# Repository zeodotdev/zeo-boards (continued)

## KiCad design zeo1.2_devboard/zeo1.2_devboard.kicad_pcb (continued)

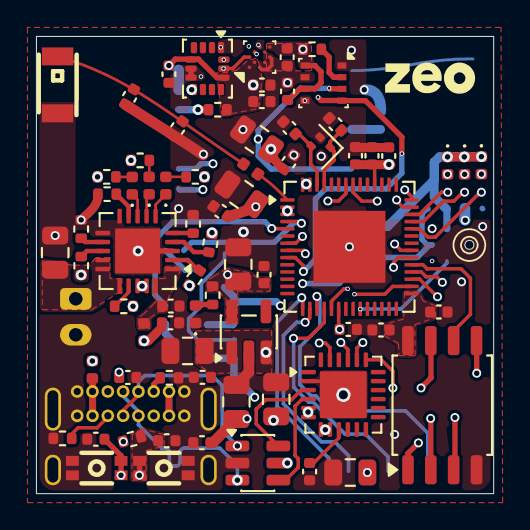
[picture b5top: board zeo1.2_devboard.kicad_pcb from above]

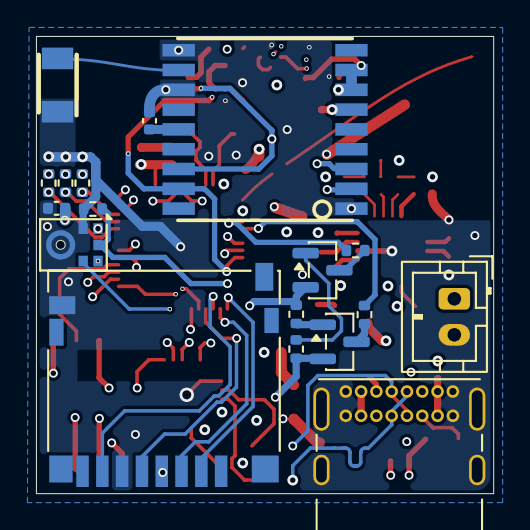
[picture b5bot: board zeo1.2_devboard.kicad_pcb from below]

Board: 4 copper layers, 25.4 x 25.4 mm, 91 parts (18 on the bottom side), 70 nets.

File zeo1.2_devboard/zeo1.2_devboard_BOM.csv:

"Id";"Designator";"Footprint";"Quantity";"Designation";"Supplier and ref";
1;"B";"KEY-SMD_4P-L2.6-W1.6-P0.80-LS3.0";1;"Boot";;;
2;"C1, C4, C16, C21, C37";"C_0805_2012Metric";5;"10uF";;;
3;"C2, C3, C5, C7, C8, C9, C10, C13, C17, C18, C20, C22, C23, C24, C26, C31, C32, C33, C34, C36";"C_0402_1005Metric";20;"0.1uF";;;
4;"C6, C14, C25";"C_0402_1005Metric";3;"1uF";;;
5;"C19";"C_0805_2012Metric";1;"4.7uF";;;
6;"C27, C28, C38";"C_0402_1005Metric";3;"10pF";;;
7;"C29";"C_0402_1005Metric";1;"0.5pF";;;
8;"C30";"C_0402_1005Metric";1;"1.2pF";;;
9;"D1, D2, D5";"LED_0402_1005Metric";3;"Red";;;
10;"D3, D6";"LED_0402_1005Metric";2;"Green";;;
11;"D4, D7";"LED_0402_1005Metric";2;"Blue";;;
12;"F1";"Fuse_0402_1005Metric";1;"1.1A PTC";;;
13;"FB1";"L_0402_1005Metric";1;"33R@100MHz";;;
14;"J1";"USB_C_Receptacle_Amphenol_12401610E4-2A_CircularHoles";1;"USB_C_Receptacle_USB2.0_14P";;;
15;"J2";"JST_ZH_B2B-ZR_1x02_P1.50mm_Vertical";1;"JST-PH Battery";;;
16;"J4";"microSD_HC_Hirose_DM3D-SF";1;"Micro_SD";;;
17;"L1";"L_0402_1005Metric";1;"2.7nH";;;
18;"MK2";"InvenSense_ICS-43434-6_3.5x2.65mm";1;"ICS-43434";;;
19;"Q2, Q3";"SOT-23";2;"BC817";;;
20;"R";"KEY-SMD_4P-L2.6-W1.6-P0.80-LS3.0";1;"RESET";;;
21;"R1, R2";"R_0402_1005Metric";2;"5.1k";;;
22;"R3";"R_0402_1005Metric";1;"2k";;;
23;"R4, R9, R16";"R_0402_1005Metric";3;"100k";;;
24;"R5";"R_0402_1005Metric";1;"20k";;;
25;"R6, R7, R8, R14, R19, R22, R23, R24, R25";"R_0402_1005Metric";9;"10k";;;
26;"R10, R20, R21, R26";"R_0402_1005Metric";4;"330R";;;
27;"R11, R12, R13";"R_0402_1005Metric";3;"470R";;;
28;"R15";"R_0402_1005Metric";1;"0R";;;
29;"TP2, TP3, TP4, TP6, TP7, TP8, TP9";"TestPoint_Pad_1.0x1.0mm";7;"TestPoint";;;
30;"U1";"SOT-23-5";1;"AP2112K-3.3";;;
31;"U2";"QFN-20-1EP_4x4mm_P0.5mm_EP2.5x2.5mm";1;"MCP73871";;;
32;"U3";"Bosch_LGA-8_2.5x2.5mm_P0.65mm_ClockwisePinNumbering";1;"BME280";;;
33;"U5";"SOT-23-6";1;"USBLC6-2SC6";;;
34;"U6";"QFN-24-1EP_4x4mm_P0.5mm_EP2.6x2.6mm";1;"CP2102N-QFN24";;;
35;"U7";"SOIC-8_5.3x5.3mm_P1.27mm";1;"W25Q128JVSIQ";;;
36;"U8";"ANT-SMD_L3.2-W1.6";1;"ANT3216LL00R2400A";;;
37;"U9";"SMD-18_L10.1-W9.7-P1.10-TL_SKG09F";1;"MAX-M10S-00B";;;
38;"U10";"QFN-56-1EP_7x7mm_P0.4mm_EP4x4mm";1;"ESP32-S3";;;
39;"U11";"LGA-14_3x2.5mm_P0.5mm_LayoutBorder3x4y";1;"LSM6DS3";;;
40;"U12";"WLCSP-12_1.56x1.56mm_P0.4mm";1;"BMM150";;;
41;"U13";"ANT-SMD_L3.2-W1.6-2";1;"W3011";;;
42;"Y1";"Crystal_SMD_WE_IQXC-240-4Pin_1.2x1.0mm";1;"40MHz";;;

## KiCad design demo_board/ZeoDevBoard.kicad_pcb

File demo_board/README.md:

# ZeoDevBoard

ESP32-S3 development board with onboard BME280 (temperature, humidity, pressure) and LSM6DS3 (6-axis IMU) sensors. This repo contains the designs, ESP-IDF firmware, and a Python plotter for visualization.

## Hardware

- **MCU:** ESP32-S3-WROOM-1 (Wi-Fi + BLE)
- **Sensors:** BME280 (I2C 0x76), LSM6DS3 (I2C 0x6A) on shared bus (GPIO8 SDA, GPIO9 SCL)
- **Power:** USB-C with MCP73871 LiPo charger + AP2112K 3.3V LDO — runs from USB or battery
- **Interface:** USB-C for flashing/debug, BOOT + RESET buttons

## Firmware

Streams sensor data over Wi-Fi as UDP broadcast JSON packets on port 12345.

- **IMU:** 100 Hz — accelerometer (m/s²) + gyroscope (deg/s)
- **BME280:** 1 Hz — temperature (°C), humidity (%RH), pressure (hPa)

### Prerequisites

- [ESP-IDF v5.4](https://docs.espressif.com/projects/esp-idf/en/v5.4/esp32s3/get-started/)

### Build and Flash

```bash
# Source ESP-IDF environment
source ~/esp/esp-idf/export.sh

# Enter firmware directory
cd firmware

# Set target and configure Wi-Fi credentials
idf.py set-target esp32s3
idf.py menuconfig  # Navigate to "ZeoDevBoard Configuration" → set SSID and password

# Build
idf.py build

# Flash (use esptool.py directly if idf.py has port permission issues)
esptool.py --chip esp32s3 -p /dev/ttyACM0 -b 460800 \
  --before default_reset --after hard_reset write_flash \
  --flash_mode dio --flash_size 2MB --flash_freq 80m \
  0x0 build/bootloader/bootloader.bin \
  0x8000 build/partition_table/partition-table.bin \
  0x10000 build/zeodevboard.bin

# Monitor serial output (optional)
idf.py -p /dev/ttyACM0 monitor
```

### Wireless Operation

Once flahsed, the board can run on battery power.

## Plotter

Displays 6 live panels: Accelerometer XYZ, Gyroscope XYZ, Temperature, Humidity, Pressure, and a status panel with packet counts.

### Run

```bash
cd plotter
python3 -m venv venv
./venv/bin/pip install -r requirements.txt
./venv/bin/python plotter.py
```

The plotter listens on UDP port 12345. Make sure your machine is on the same network as the board.

### UDP Packet Format

IMU (100 Hz):
```json
{"type":"imu","ts":1234,"ax":0.12,"ay":-0.05,"az":-9.81,"gx":1.2,"gy":-0.3,"gz":0.1}
```

Environment (1 Hz):
```json
{"type":"env","ts":1234,"temp":25.3,"hum":45.2,"press":1013.4}
```

`ts` is milliseconds since boot.

## Project Structure

```
demo_board/
├── firmware/
│   ├── CMakeLists.txt
│   ├── sdkconfig.defaults
│   └── main/
│       ├── CMakeLists.txt
│       ├── Kconfig.projbuild      # Wi-Fi SSID/password config
│       ├── main.c                 # App entry, FreeRTOS tasks
│       ├── wifi.c / wifi.h        # Wi-Fi STA connection
│       ├── sensors.c / sensors.h  # BME280 + LSM6DS3 I2C drivers
│       └── udp_sender.c / udp_sender.h  # UDP broadcast
├── plotter/
│   ├── plotter.py
│   └── requirements.txt
├── ZeoDevBoard.kicad_sch          # Root schematic
├── mcu.kicad_sch                  # MCU sheet
├── power_supply.kicad_sch         # Power supply sheet
├── sensors.kicad_sch              # Sensors sheet
├── ZeoDevBoard.kicad_pcb          # PCB layout
└── README.md
```

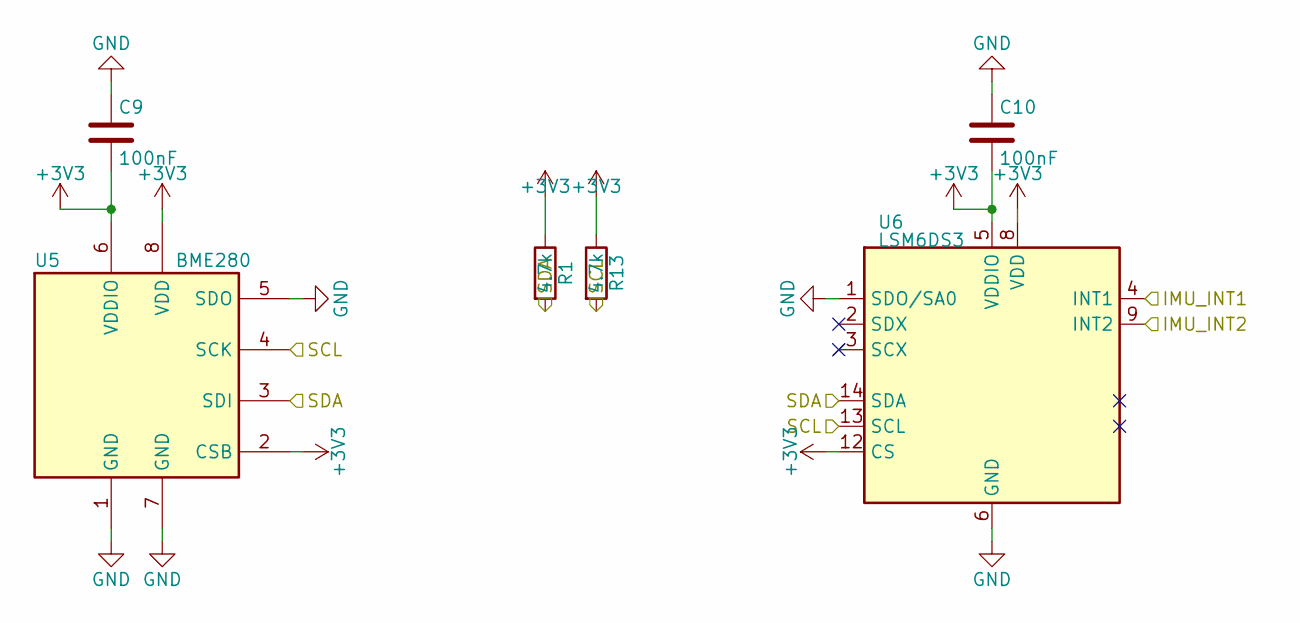
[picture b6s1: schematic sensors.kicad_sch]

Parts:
C9, C10: 100nF; C_0402_1005Metric
R1, R13: 4.7k; R_0603_1608Metric
U5: BME280; Bosch_LGA-8_2.5x2.5mm_P0.65mm_ClockwisePinNumbering
U6: LSM6DS3; LGA-14_3x2.5mm_P0.5mm_LayoutBorder3x4y

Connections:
+3V3: C9.2, C10.2, R1.1, R13.1, U5.2 (CSB), U5.6 (VDDIO), U5.8 (VDD), U6.5 (VDDIO), U6.8 (VDD), U6.12 (CS); also elsewhere on the board
/IMU_INT1: U6.4 (INT1); also elsewhere on the board
/IMU_INT2: U6.9 (INT2); also elsewhere on the board
/SCL: R13.2, U5.4 (SCK), U6.13 (SCL); also elsewhere on the board
/SDA: R1.2, U5.3 (SDI), U6.14 (SDA); also elsewhere on the board

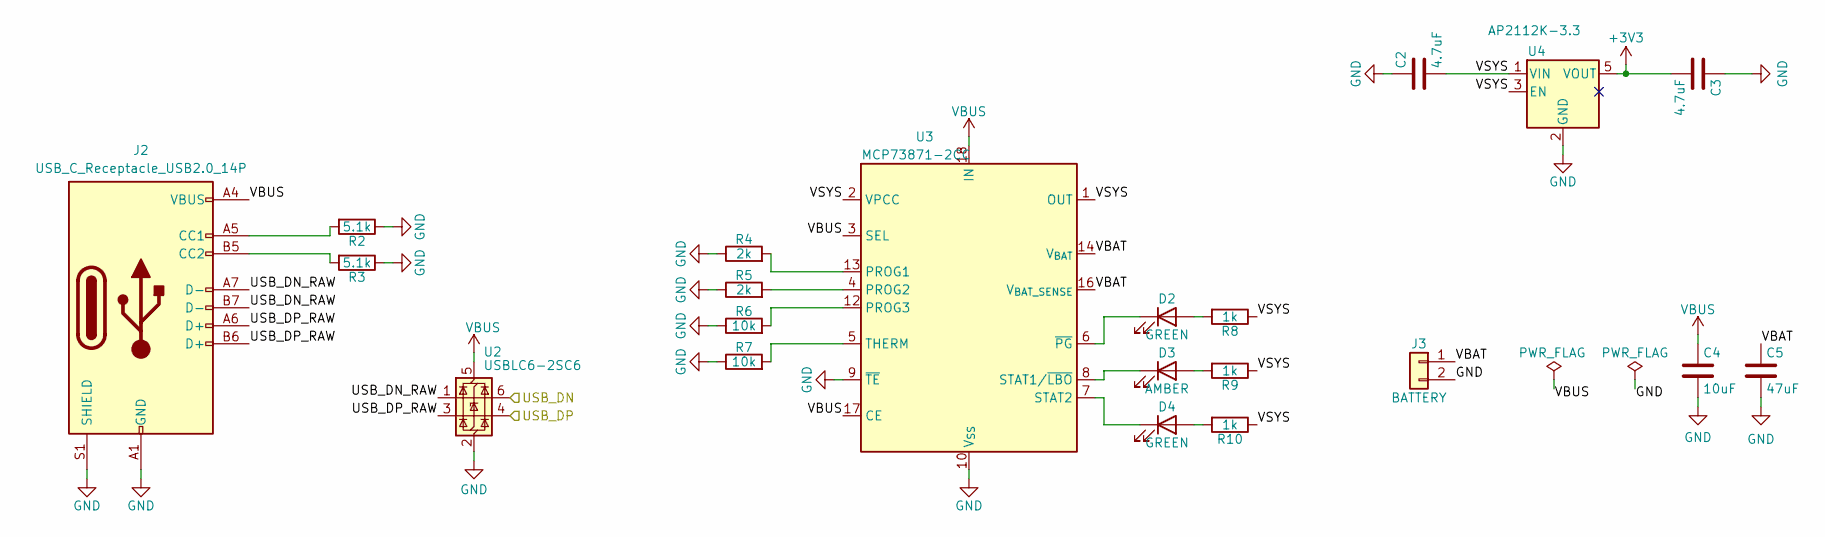
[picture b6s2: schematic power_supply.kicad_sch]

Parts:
C2, C3: 4.7uF; C_0805_2012Metric
C4: 10uF; C_0805_2012Metric
C5: 47uF; C_1206_3216Metric
D2, D4: GREEN; LED_0603_1608Metric
D3: AMBER; LED_0603_1608Metric
J2: USB_C_Receptacle_USB2.0_14P; USB_C_Receptacle_Amphenol_12401610E4-2A
J3: BATTERY; JST_PH_B2B-PH-K_1x02_P2.00mm_Vertical
R2, R3: 5.1k; R_0603_1608Metric
R4, R5: 2k; R_0603_1608Metric
R6, R7: 10k; R_0603_1608Metric
R8, R9, R10: 1k; R_0603_1608Metric
U2: USBLC6-2SC6; SOT-23-6
U3: MCP73871-2CC; QFN-20-1EP_4x4mm_P0.5mm_EP2.5x2.5mm
U4: AP2112K-3.3; SOT-23-5

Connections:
+3V3: C3.2, U4.5 (VOUT); also elsewhere on the board
/Power Supply/USB_DN_RAW: J2.A7 (D-), J2.B7 (D-), U2.1 (I/O1)
/Power Supply/USB_DP_RAW: J2.A6 (D+), J2.B6 (D+), U2.3 (I/O2)
/Power Supply/VBAT: C5.1, J3.1, U3.14 (V_{BAT}), U3.15 (V_{BAT}), U3.16 (V_{BAT_SENSE})
/Power Supply/VSYS: C2.2, R8.1, R9.1, R10.1, U3.1 (OUT), U3.2 (VPCC), U3.20 (OUT), U4.1 (VIN), U4.3 (EN)
/USB_DN: U2.6 (I/O1); also elsewhere on the board
/USB_DP: U2.4 (I/O2); also elsewhere on the board
unnamed: D2.2 (A), R8.2
unnamed: D2.1 (K), U3.6 (~PG)
unnamed: D3.2 (A), R9.2
unnamed: D3.1 (K), U3.8 (STAT1/~LBO)
unnamed: D4.2 (A), R10.2
unnamed: D4.1 (K), U3.7 (STAT2)
unnamed: J2.A5 (CC1), R2.2
unnamed: J2.B5 (CC2), R3.2
unnamed: R4.2, U3.13 (PROG1)
unnamed: R5.2, U3.4 (PROG2)
unnamed: R6.2, U3.12 (PROG3)
unnamed: R7.2, U3.5 (THERM)

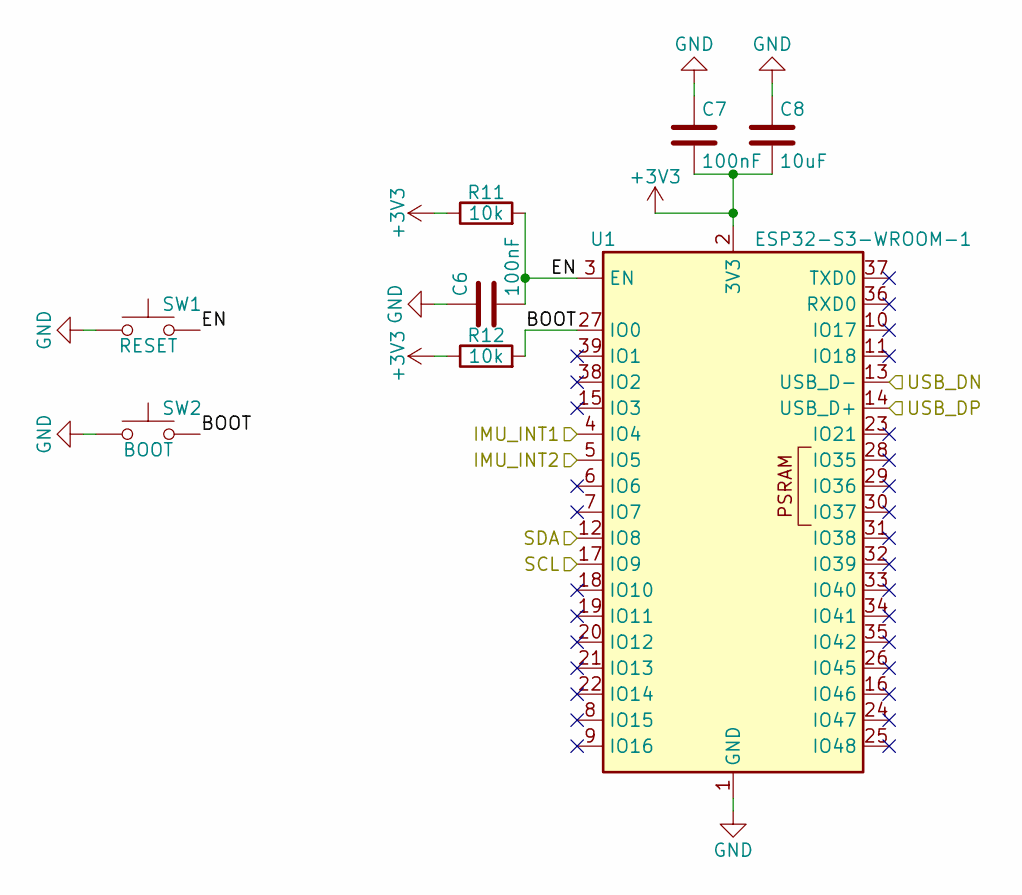
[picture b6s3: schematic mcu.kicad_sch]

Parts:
C6, C7: 100nF; C_0402_1005Metric
C8: 10uF; C_0805_2012Metric
R11, R12: 10k; R_0603_1608Metric
SW1: RESET; SW_SPST_B3U-1000P-B
SW2: BOOT; SW_SPST_B3U-1000P-B
U1: ESP32-S3-WROOM-1

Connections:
+3V3: C7.2, C8.2, R11.1, R12.1, U1.2 (3V3); also elsewhere on the board
/IMU_INT1: U1.4 (IO4); also elsewhere on the board
/IMU_INT2: U1.5 (IO5); also elsewhere on the board
/MCU/BOOT: R12.2, SW2.2, U1.27 (IO0)
/MCU/EN: C6.2, R11.2, SW1.2, U1.3 (EN)
/SCL: U1.17 (IO9); also elsewhere on the board
/SDA: U1.12 (IO8); also elsewhere on the board
/USB_DN: U1.13 (USB_D-); also elsewhere on the board
/USB_DP: U1.14 (USB_D+); also elsewhere on the board

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
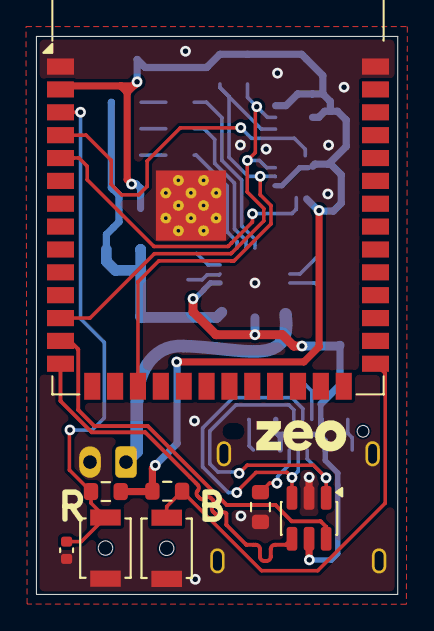
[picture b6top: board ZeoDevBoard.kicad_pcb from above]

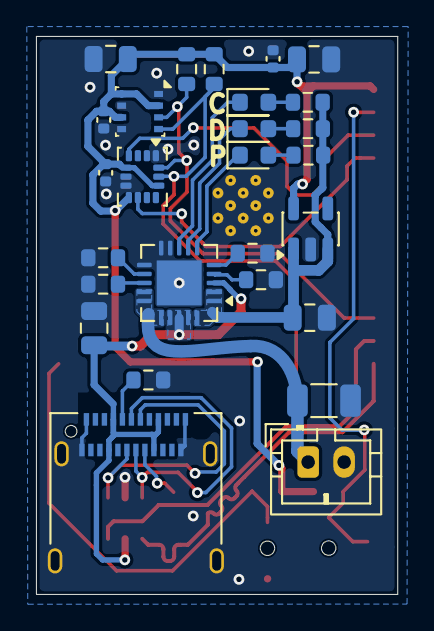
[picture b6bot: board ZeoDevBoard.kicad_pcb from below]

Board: 2 copper layers, 20.1 x 31.0 mm, 35 parts (27 on the bottom side), 27 nets.

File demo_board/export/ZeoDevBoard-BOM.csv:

Id,Designator,Footprint,Quantity,Comment,Supplier and ref
1,"C2, C3",C_0805_2012Metric,2,4.7uF,
2,"C4, C8",C_0805_2012Metric,2,10uF,
3,C5,C_1206_3216Metric,1,47uF,
4,"C6, C7, C9, C10",C_0402_1005Metric,4,100nF,
5,"D2, D4",LED_0603_1608Metric,2,GREEN,
6,D3,LED_0603_1608Metric,1,AMBER,
7,J2,USB_C_Receptacle_Amphenol_12401610E4-2A,1,USB_C_Receptacle_USB2.0_14P,
8,J3,JST_PH_B2B-PH-K_1x02_P2.00mm_Vertical,1,BATTERY,
9,"R1, R13",R_0603_1608Metric,2,4.7k,
10,"R2, R3",R_0603_1608Metric,2,5.1k,
11,"R4, R5",R_0603_1608Metric,2,2k,
12,"R6, R7, R11, R12",R_0603_1608Metric,4,10k,
13,"R8, R9, R10",R_0603_1608Metric,3,1k,
14,SW1,SW_SPST_B3U-1000P-B,1,RESET,
15,SW2,SW_SPST_B3U-1000P-B,1,BOOT,
16,U1,ESP32-S3-WROOM-1,1,ESP32-S3-WROOM-1,
17,U2,SOT-23-6,1,USBLC6-2SC6,
18,U3,QFN-20-1EP_4x4mm_P0.5mm_EP2.5x2.5mm,1,MCP73871-2CC,
19,U4,SOT-23-5,1,AP2112K-3.3,
20,U5,Bosch_LGA-8_2.5x2.5mm_P0.65mm_ClockwisePinNumbering,1,BME280,
21,U6,LGA-14_3x2.5mm_P0.5mm_LayoutBorder3x4y,1,LSM6DS3,

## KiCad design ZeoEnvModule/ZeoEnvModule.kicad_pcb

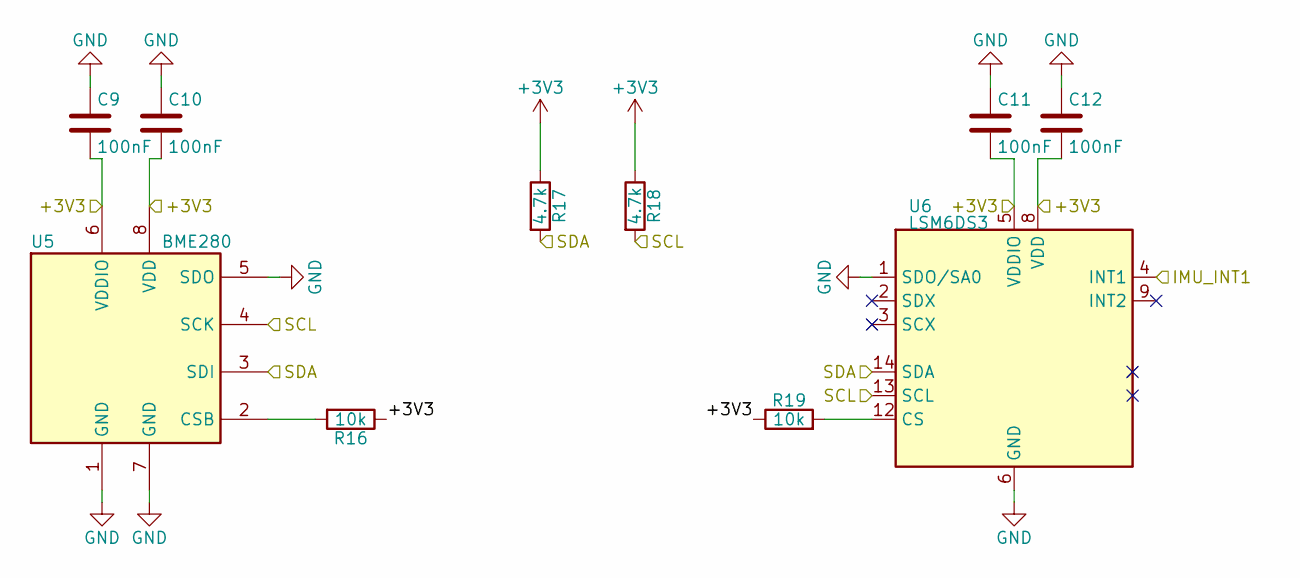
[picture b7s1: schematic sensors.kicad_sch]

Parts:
C9, C10, C11, C12: 100nF; C_0402_1005Metric
R16, R19: 10k; R_0402_1005Metric
R17, R18: 4.7k; R_0402_1005Metric
U5: BME280; Bosch_LGA-8_2.5x2.5mm_P0.65mm_ClockwisePinNumbering
U6: LSM6DS3; LGA-14_3x2.5mm_P0.5mm_LayoutBorder3x4y

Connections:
+3V3: C9.2, C10.2, C11.2, C12.2, R16.1, R17.1, R18.1, R19.1, U5.6 (VDDIO), U5.8 (VDD), U6.5 (VDDIO), U6.8 (VDD); also elsewhere on the board
/IMU_INT1: U6.4 (INT1); also elsewhere on the board
/SCL: R18.2, U5.4 (SCK), U6.13 (SCL); also elsewhere on the board
/SDA: R17.2, U5.3 (SDI), U6.14 (SDA); also elsewhere on the board
unnamed: R16.2, U5.2 (CSB)
unnamed: R19.2, U6.12 (CS)

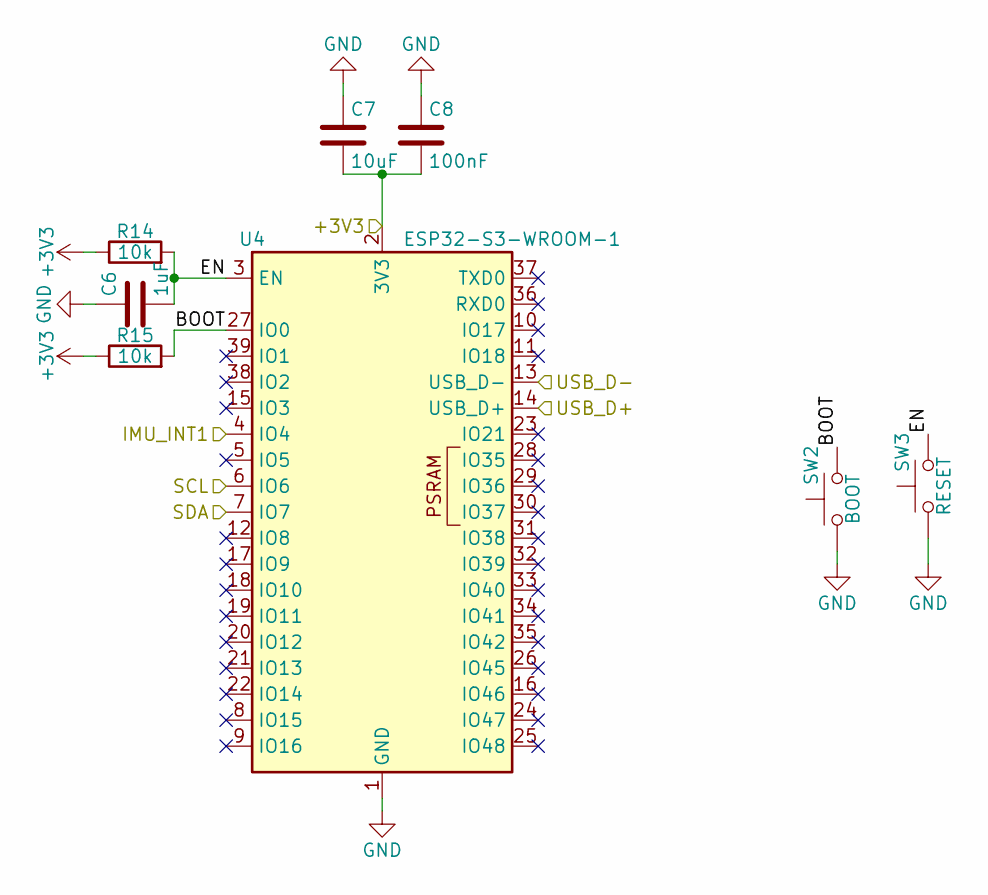
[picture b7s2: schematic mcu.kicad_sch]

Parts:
C6: 1uF; C_0402_1005Metric
C7: 10uF; C_0805_2012Metric
C8: 100nF; C_0402_1005Metric
R14, R15: 10k; R_0402_1005Metric
SW2: BOOT; SW_SPST_B3U-1000P-B
SW3: RESET; SW_SPST_B3U-1000P-B
U4: ESP32-S3-WROOM-1

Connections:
+3V3: C7.2, C8.2, R14.1, R15.1, U4.2 (3V3); also elsewhere on the board
/IMU_INT1: U4.4 (IO4); also elsewhere on the board
/MCU/BOOT: R15.2, SW2.2, U4.27 (IO0)
/MCU/EN: C6.2, R14.2, SW3.2, U4.3 (EN)
/SCL: U4.6 (IO6); also elsewhere on the board
/SDA: U4.7 (IO7); also elsewhere on the board
/USB_D+: U4.14 (USB_D+); also elsewhere on the board
/USB_D-: U4.13 (USB_D-); also elsewhere on the board

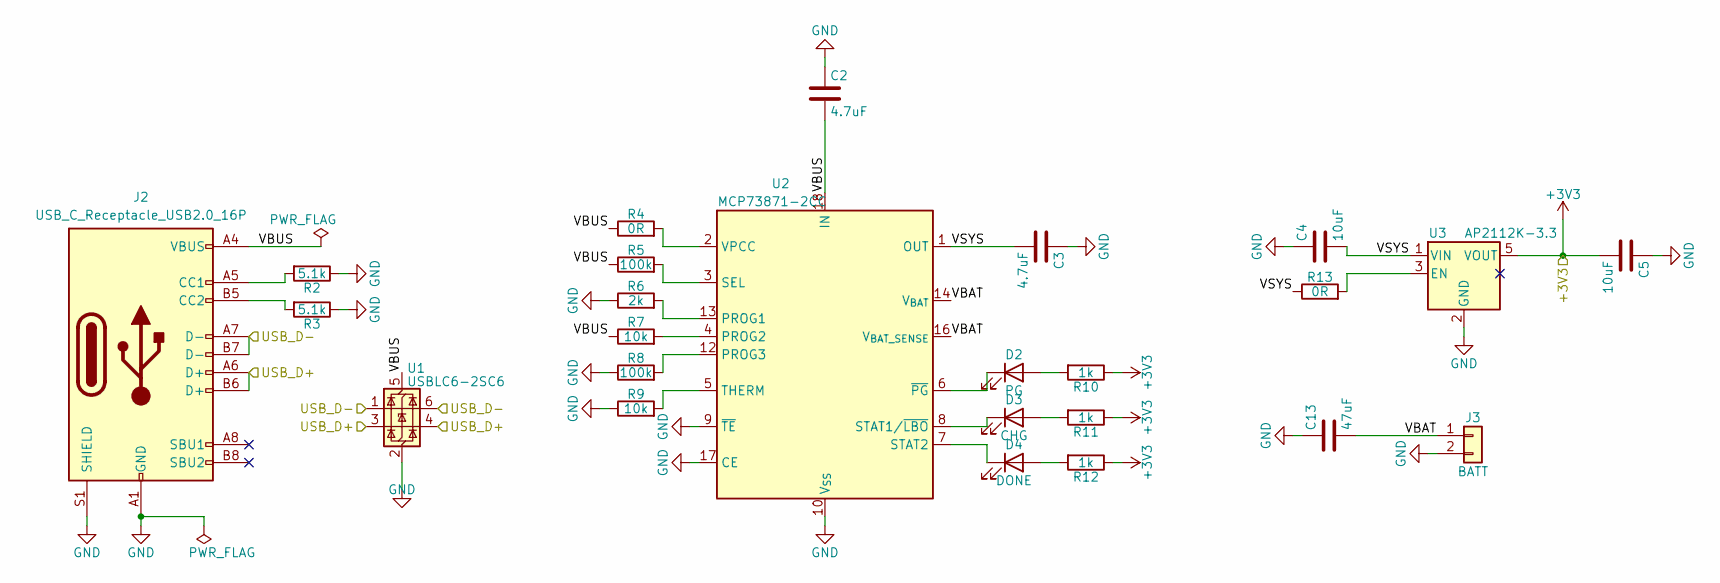
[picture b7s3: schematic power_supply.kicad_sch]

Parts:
C2, C3: 4.7uF; C_0603_1608Metric
C4, C5: 10uF; C_0805_2012Metric
C13: 47uF; C_1210_3225Metric
D2: PG; LED_0603_1608Metric
D3: CHG; LED_0603_1608Metric
D4: DONE; LED_0603_1608Metric
J2: USB_C_Receptacle_USB2.0_16P; USB_C_Receptacle_HRO_TYPE-C-31-M-12
J3: BATT; JST_PH_B2B-PH-K_1x02_P2.00mm_Vertical
R2, R3: 5.1k; R_0402_1005Metric
R4, R13: 0R; R_0402_1005Metric
R5, R8: 100k; R_0402_1005Metric
R6: 2k; R_0402_1005Metric
R7, R9: 10k; R_0402_1005Metric
R10, R11, R12: 1k; R_0402_1005Metric
U1: USBLC6-2SC6; SOT-23-6
U2: MCP73871-2CC; QFN-20-1EP_4x4mm_P0.5mm_EP2.5x2.5mm
U3: AP2112K-3.3; SOT-23-5

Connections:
+3V3: C5.2, R10.1, R11.1, R12.1, U3.5 (VOUT); also elsewhere on the board
/Power Supply/VBAT: C13.2, J3.1, U2.14 (V_{BAT}), U2.15 (V_{BAT}), U2.16 (V_{BAT_SENSE})
/Power Supply/VSYS: C3.2, C4.2, R13.1, U2.1 (OUT), U2.20 (OUT), U3.1 (VIN)
/USB_D+: J2.A6 (D+), J2.B6 (D+), U1.3 (I/O2), U1.4 (I/O2); also elsewhere on the board
/USB_D-: J2.A7 (D-), J2.B7 (D-), U1.1 (I/O1), U1.6 (I/O1); also elsewhere on the board
unnamed: D2.2 (A), R10.2
unnamed: D2.1 (K), U2.6 (~PG)
unnamed: D3.2 (A), R11.2
unnamed: D3.1 (K), U2.8 (STAT1/~LBO)
unnamed: D4.2 (A), R12.2
unnamed: D4.1 (K), U2.7 (STAT2)
unnamed: J2.A5 (CC1), R2.2
unnamed: J2.B5 (CC2), R3.2
unnamed: R6.2, U2.13 (PROG1)
unnamed: R7.2, U2.4 (PROG2)
unnamed: R8.2, U2.12 (PROG3)
unnamed: R5.2, U2.3 (SEL)
unnamed: R9.2, U2.5 (THERM)
unnamed: R4.2, U2.2 (VPCC)
unnamed: R13.2, U3.3 (EN)

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
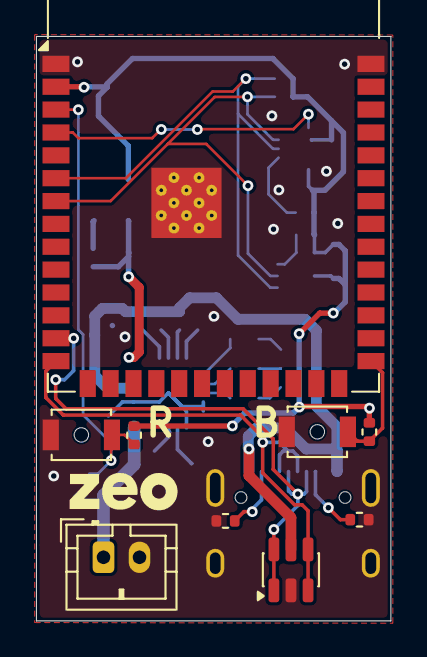
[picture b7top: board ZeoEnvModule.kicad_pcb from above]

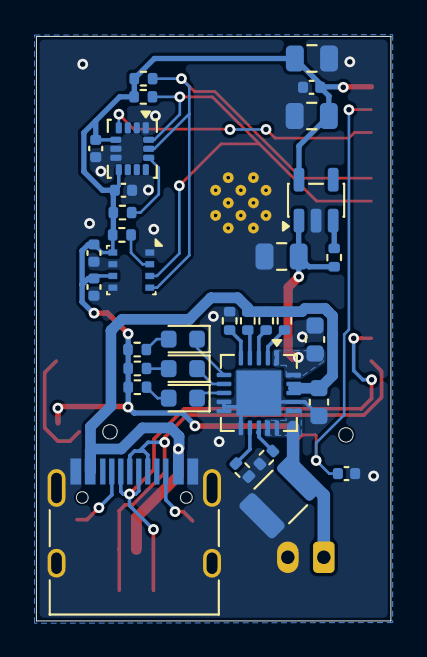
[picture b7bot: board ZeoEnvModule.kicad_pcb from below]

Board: 2 copper layers, 19.7 x 32.5 mm, 43 parts (34 on the bottom side), 29 nets.

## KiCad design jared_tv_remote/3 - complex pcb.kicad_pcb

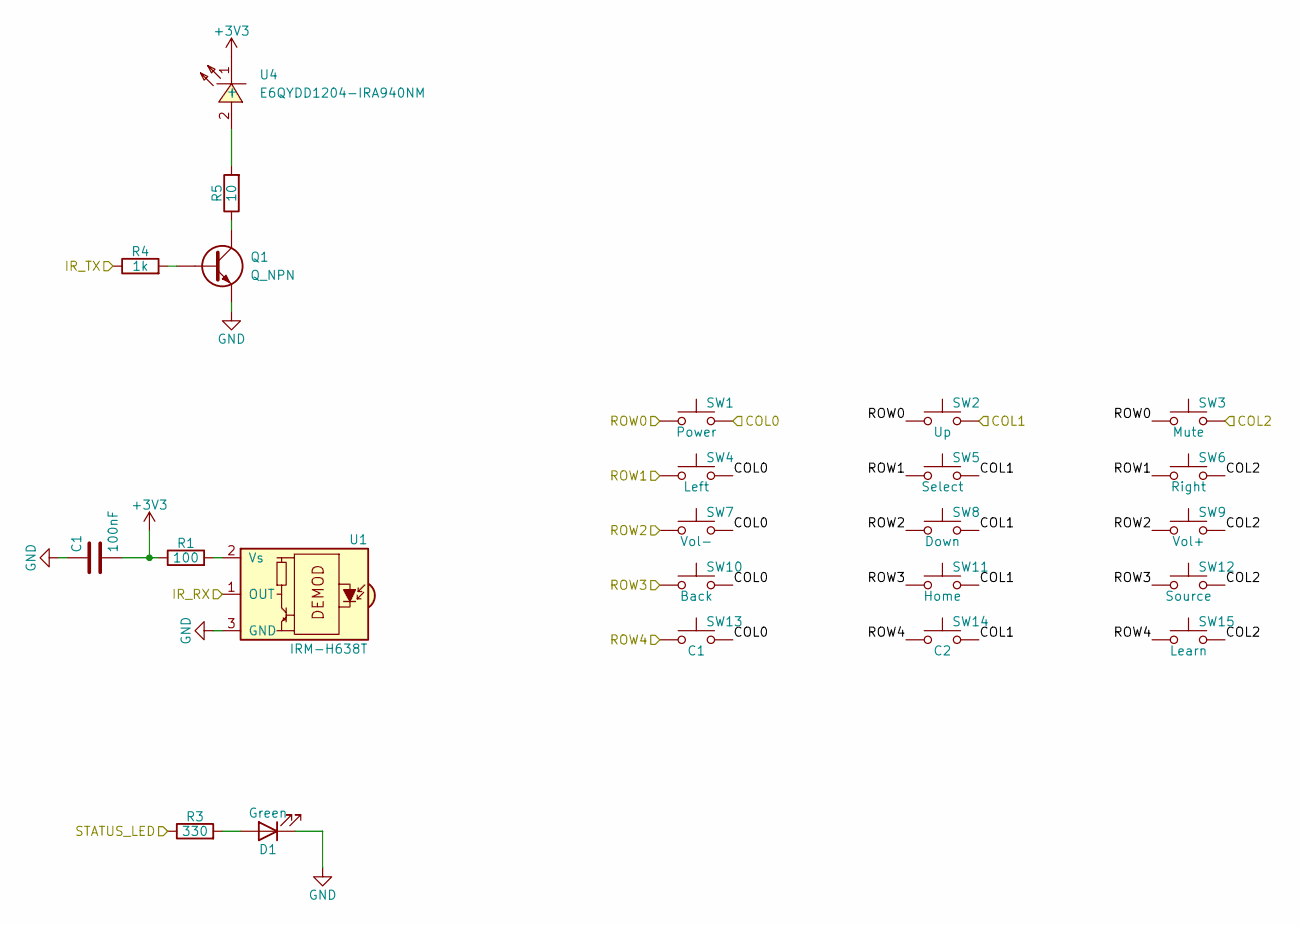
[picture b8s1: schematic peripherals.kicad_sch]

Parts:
C1: 100nF; C_0402_1005Metric
D1: Green; LED_0603_1608Metric
Q1: Q_NPN; SOT-23
R1: 100; R_0402_1005Metric
R3: 330; R_0402_1005Metric
R4: 1k; R_0402_1005Metric
R5: 10; R_0805_2012Metric
SW1: Power; SW_SPST_B3U-1000P
SW2: Up; SW_SPST_B3U-1000P
SW3: Mute; SW_SPST_B3U-1000P
SW4: Left; SW_SPST_B3U-1000P
SW5: Select; SW_SPST_B3U-1000P
SW6: Right; SW_SPST_B3U-1000P
SW7: Vol-; SW_SPST_B3U-1000P
SW8: Down; SW_SPST_B3U-1000P
SW9: Vol+; SW_SPST_B3U-1000P
SW10: Back; SW_SPST_B3U-1000P
SW11: Home; SW_SPST_B3U-1000P
SW12: Source; SW_SPST_B3U-1000P
SW13: C1; SW_SPST_B3U-1000P
SW14: C2; SW_SPST_B3U-1000P
SW15: Learn; SW_SPST_B3U-1000P
U1: IRM-H638T; Everlight_IRM-H6xxT
U4: E6QYDD1204-IRA940NM; LED-SMD_L3.2-W2.1-R-FD; LCSC Part C396649

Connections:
+3V3: C1.2, R1.1, U4.1 (-); also elsewhere on the board
/COL0: SW1.2, SW4.2, SW7.2, SW10.2, SW13.2; also elsewhere on the board
/COL1: SW2.2, SW5.2, SW8.2, SW11.2, SW14.2; also elsewhere on the board
/COL2: SW3.2, SW6.2, SW9.2, SW12.2, SW15.2; also elsewhere on the board
/IR_RX: U1.1 (OUT); also elsewhere on the board
/IR_TX: R4.1; also elsewhere on the board
/ROW0: SW1.1, SW2.1, SW3.1; also elsewhere on the board
/ROW1: SW4.1, SW5.1, SW6.1; also elsewhere on the board
/ROW2: SW7.1, SW8.1, SW9.1; also elsewhere on the board
/ROW3: SW10.1, SW11.1, SW12.1; also elsewhere on the board
/ROW4: SW13.1, SW14.1, SW15.1; also elsewhere on the board
/STATUS_LED: R3.1; also elsewhere on the board
unnamed: D1.2 (A), R3.2
unnamed 16: R5.2, U4.2 (+); also elsewhere on the board
unnamed: Q1.1 (B), R4.2
unnamed: Q1.2 (C), R5.1
unnamed: R1.2, U1.2 (Vs)

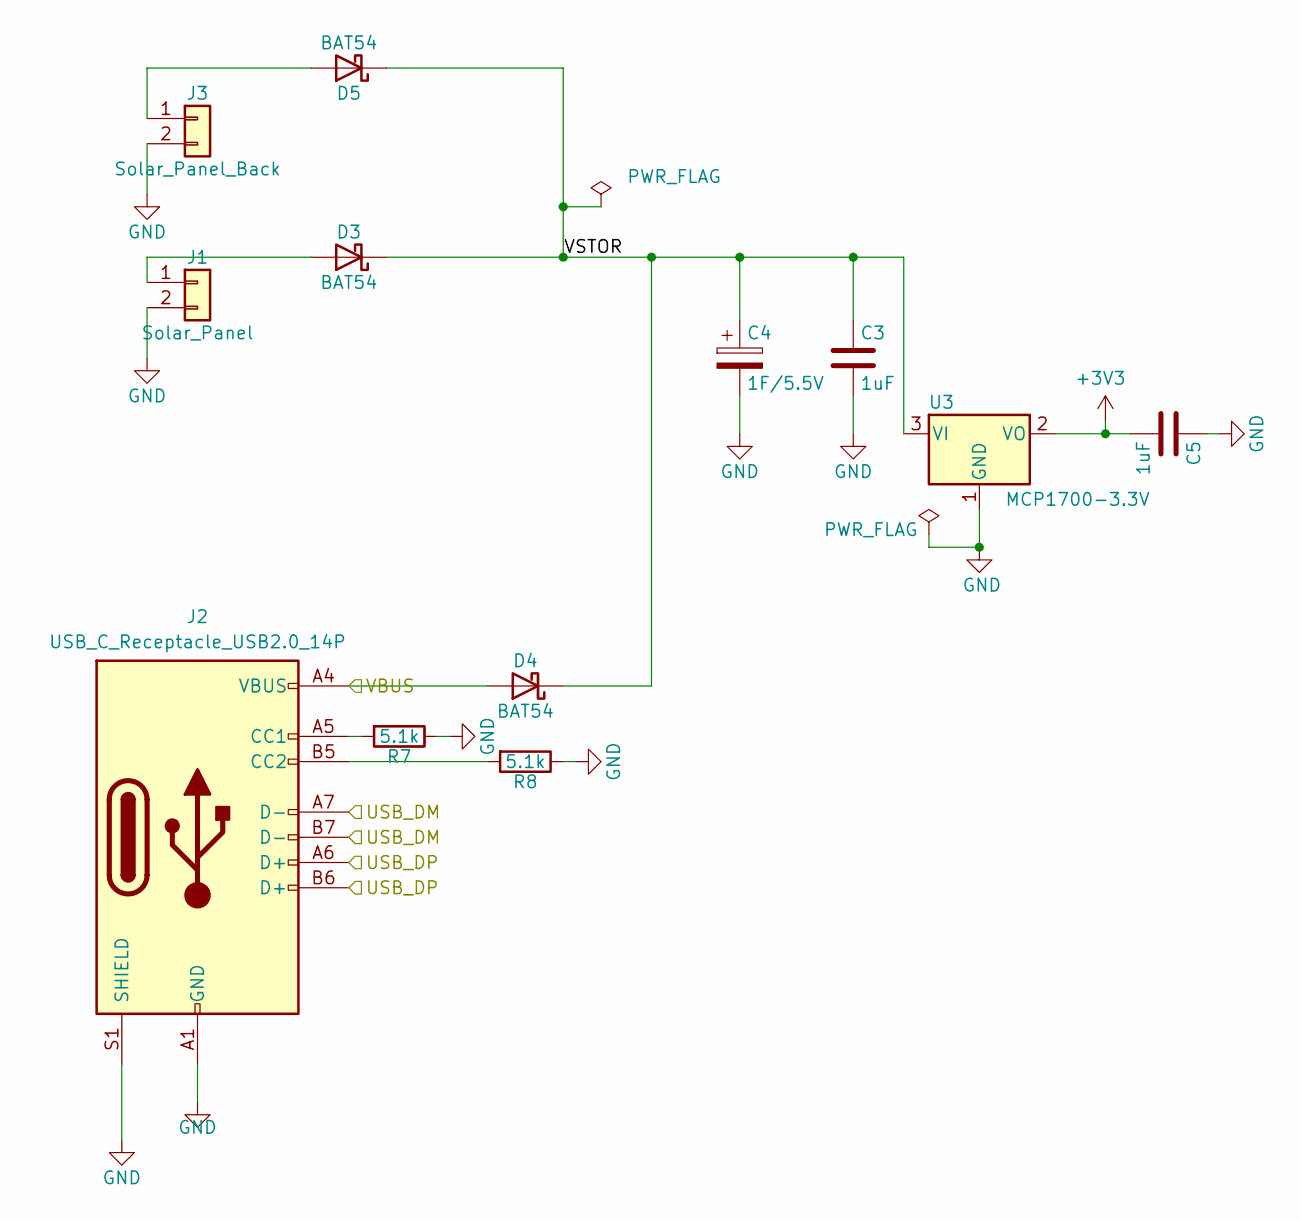
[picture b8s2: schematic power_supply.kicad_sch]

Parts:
C3, C5: 1uF; C_0402_1005Metric
C4: 1F/5.5V; C_1210_3225Metric
D3, D4, D5: BAT54; D_SOD-323
J1: Solar_Panel; SolderWire-0.5sqmm_1x02_P4.6mm_D0.9mm_OD2.1mm
J2: USB_C_Receptacle_USB2.0_14P; USB_C_Receptacle_HRO_TYPE-C-31-M-12
J3: Solar_Panel_Back; SolderWire-0.5sqmm_1x02_P4.6mm_D0.9mm_OD2.1mm
R7, R8: 5.1k; R_0402_1005Metric
U3: MCP1700-3.3V; SOT-23

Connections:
+3V3: C5.2, U3.2 (VO); also elsewhere on the board
/USB_DM: J2.A7 (D-), J2.B7 (D-); also elsewhere on the board
/USB_DP: J2.A6 (D+), J2.B6 (D+); also elsewhere on the board
/VBUS: D4.2 (A), J2.A4 (VBUS), J2.A9 (VBUS), J2.B4 (VBUS), J2.B9 (VBUS); also elsewhere on the board
unnamed: D3.2 (A), J1.1
unnamed: D5.2 (A), J3.1
unnamed: J2.A5 (CC1), R7.2
unnamed: J2.B5 (CC2), R8.2

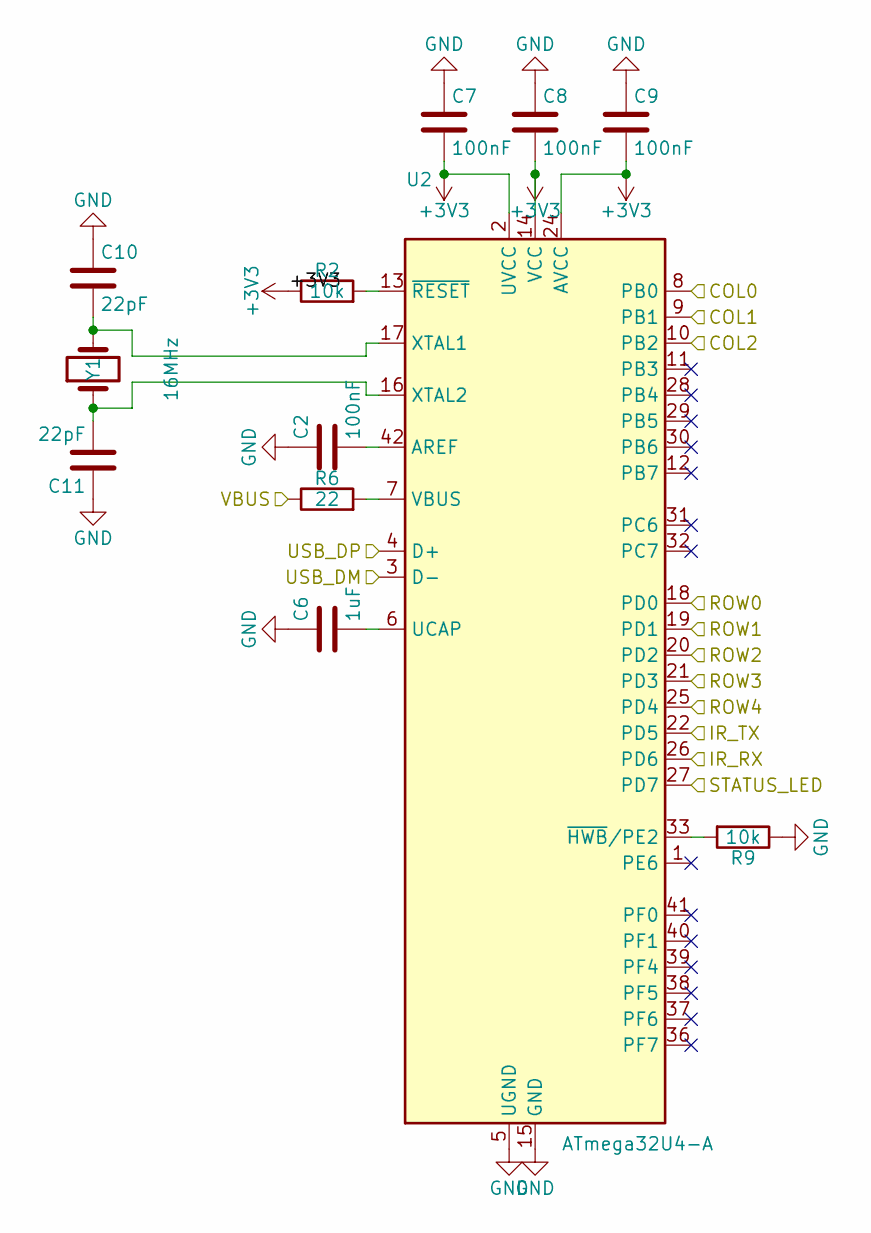
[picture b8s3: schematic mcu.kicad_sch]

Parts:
C2, C7, C8, C9: 100nF; C_0402_1005Metric
C6: 1uF; C_0402_1005Metric
C10, C11: 22pF; C_0402_1005Metric
R2, R9: 10k; R_0402_1005Metric
R6: 22; R_0402_1005Metric
U2: ATmega32U4-A; TQFP-44_10x10mm_P0.8mm
Y1: 16MHz; Crystal_SMD_3215-2Pin_3.2x1.5mm

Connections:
+3V3: C7.2, C8.2, C9.2, R2.1, U2.2 (UVCC), U2.14 (VCC), U2.24 (AVCC), U2.34 (VCC), U2.44 (AVCC); also elsewhere on the board
/COL0: U2.8 (PB0); also elsewhere on the board
/COL1: U2.9 (PB1); also elsewhere on the board
/COL2: U2.10 (PB2); also elsewhere on the board
/IR_RX: U2.26 (PD6); also elsewhere on the board
/IR_TX: U2.22 (PD5); also elsewhere on the board
/ROW0: U2.18 (PD0); also elsewhere on the board
/ROW1: U2.19 (PD1); also elsewhere on the board
/ROW2: U2.20 (PD2); also elsewhere on the board
/ROW3: U2.21 (PD3); also elsewhere on the board
/ROW4: U2.25 (PD4); also elsewhere on the board
/STATUS_LED: U2.27 (PD7); also elsewhere on the board
/USB_DM: U2.3 (D-); also elsewhere on the board
/USB_DP: U2.4 (D+); also elsewhere on the board
/VBUS: R6.1; also elsewhere on the board
unnamed: C2.2, U2.42 (AREF)
unnamed: C6.2, U2.6 (UCAP)
unnamed: R6.2, U2.7 (VBUS)
unnamed: C10.2, U2.17 (XTAL1), Y1.2
unnamed: C11.2, U2.16 (XTAL2), Y1.1
unnamed: R9.2, U2.33 (~HWB/PE2)
unnamed: R2.2, U2.13 (~RESET)

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
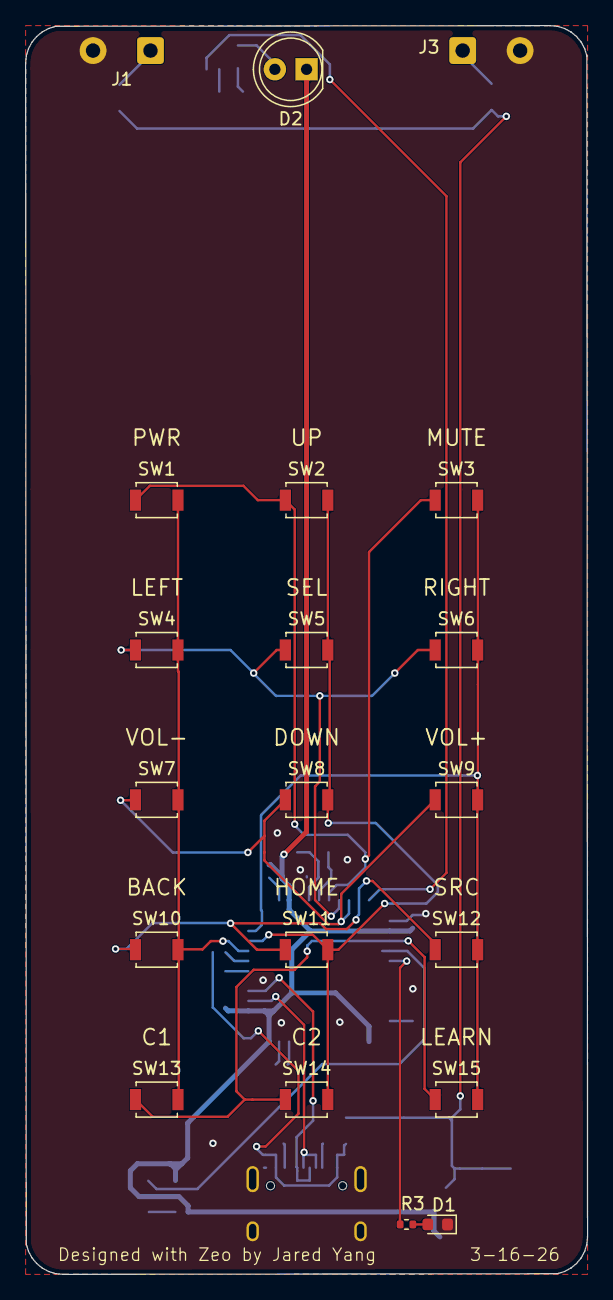
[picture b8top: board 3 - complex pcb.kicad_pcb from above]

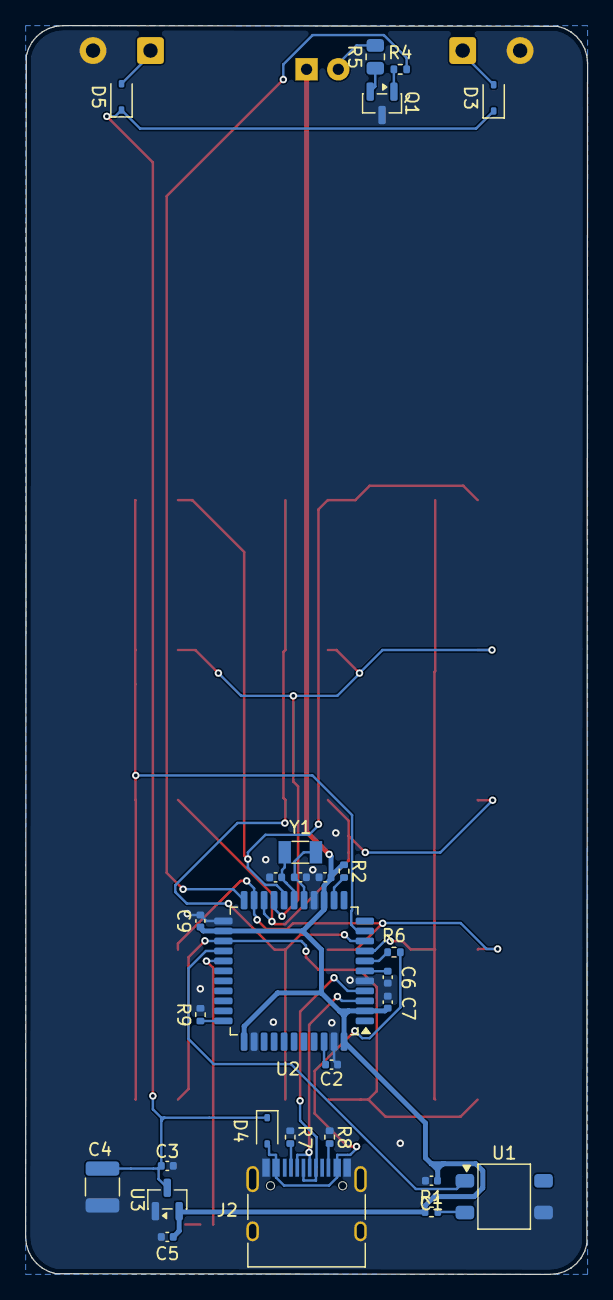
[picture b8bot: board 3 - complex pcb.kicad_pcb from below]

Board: 2 copper layers, 45.0 x 100.0 mm, 48 parts (28 on the bottom side), 33 nets.

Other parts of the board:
D2: IR_940nm; LED_D5.0mm

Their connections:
+3V3: D2.1 (K); also elsewhere on the board
unnamed 16: D2.2 (A); also elsewhere on the board

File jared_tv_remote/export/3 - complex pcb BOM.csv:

Id,Designator,Footprint,Quantity,Comment,Supplier and ref
1,"C1, C2, C7, C8, C9",C_0402_1005Metric,5,100nF,
2,"C3, C5, C6",C_0402_1005Metric,3,1uF,
3,C4,C_1210_3225Metric,1,1F/5.5V,
4,"C10, C11",C_0402_1005Metric,2,22pF,
5,D1,LED_0603_1608Metric,1,Green,
6,D2,LED_D5.0mm,1,IR_940nm,
7,"D3, D4, D5",D_SOD-323,3,BAT54,
8,J1,SolderWire-0.5sqmm_1x02_P4.6mm_D0.9mm_OD2.1mm,1,Solar_Panel,
9,J2,USB_C_Receptacle_HRO_TYPE-C-31-M-12,1,USB_C_Receptacle_USB2.0_14P,
10,J3,SolderWire-0.5sqmm_1x02_P4.6mm_D0.9mm_OD2.1mm,1,Solar_Panel_Back,
11,Q1,SOT-23,1,Q_NPN,
12,R1,R_0402_1005Metric,1,100,
13,"R2, R9",R_0402_1005Metric,2,10k,
14,R3,R_0402_1005Metric,1,330,
15,R4,R_0402_1005Metric,1,1k,
16,R5,R_0805_2012Metric,1,10,
17,R6,R_0402_1005Metric,1,22,
18,"R7, R8",R_0402_1005Metric,2,5.1k,
19,SW1,SW_SPST_B3U-1000P,1,Power,
20,SW2,SW_SPST_B3U-1000P,1,Up,
21,SW3,SW_SPST_B3U-1000P,1,Mute,
22,SW4,SW_SPST_B3U-1000P,1,Left,
23,SW5,SW_SPST_B3U-1000P,1,Select,
24,SW6,SW_SPST_B3U-1000P,1,Right,
25,SW7,SW_SPST_B3U-1000P,1,Vol-,
26,SW8,SW_SPST_B3U-1000P,1,Down,
27,SW9,SW_SPST_B3U-1000P,1,Vol+,
28,SW10,SW_SPST_B3U-1000P,1,Back,
29,SW11,SW_SPST_B3U-1000P,1,Home,
30,SW12,SW_SPST_B3U-1000P,1,Source,
31,SW13,SW_SPST_B3U-1000P,1,C1,
32,SW14,SW_SPST_B3U-1000P,1,C2,
33,SW15,SW_SPST_B3U-1000P,1,Learn,
34,U1,Everlight_IRM-H6xxT,1,IRM-H638T,
35,U2,TQFP-44_10x10mm_P0.8mm,1,ATmega32U4-A,
36,U3,SOT-23,1,MCP1700-3.3V,
37,Y1,Crystal_SMD_3215-2Pin_3.2x1.5mm,1,16MHz,

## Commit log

2026-03-18 First boards
2026-03-19 Add IR Remote PCB
2026-03-24 demo board
2026-03-25 new board
2026-03-25 boards
2026-03-27 new demo board
2026-04-02 new boards
2026-04-03 Enhance README with details about Zeo boards
    Added a detailed description of the Zeo boards repository, including examples of boards and their purposes.
2026-04-04 1.2 updates
2026-04-12 holes
2026-04-17 demo_board firmware
2026-04-21 images
2026-04-22 Update tv remote plan
2026-05-07 Add tv remote firmware
    Bare-metal avr-gcc implementation per plan.md: 5x3 button matrix scan
    with INT0-3 low-level wake from power-down, Timer1 38kHz IR carrier on
    OC1A, Timer3-sampled IR receive at 100us, and raw learn-and-replay
    codes stored in EEPROM (16-byte header + 14 x 72-byte slots, exact 1KB
    fit). Press Learn (SW15) then any button to capture an IR frame from
    another remote into that slot.
